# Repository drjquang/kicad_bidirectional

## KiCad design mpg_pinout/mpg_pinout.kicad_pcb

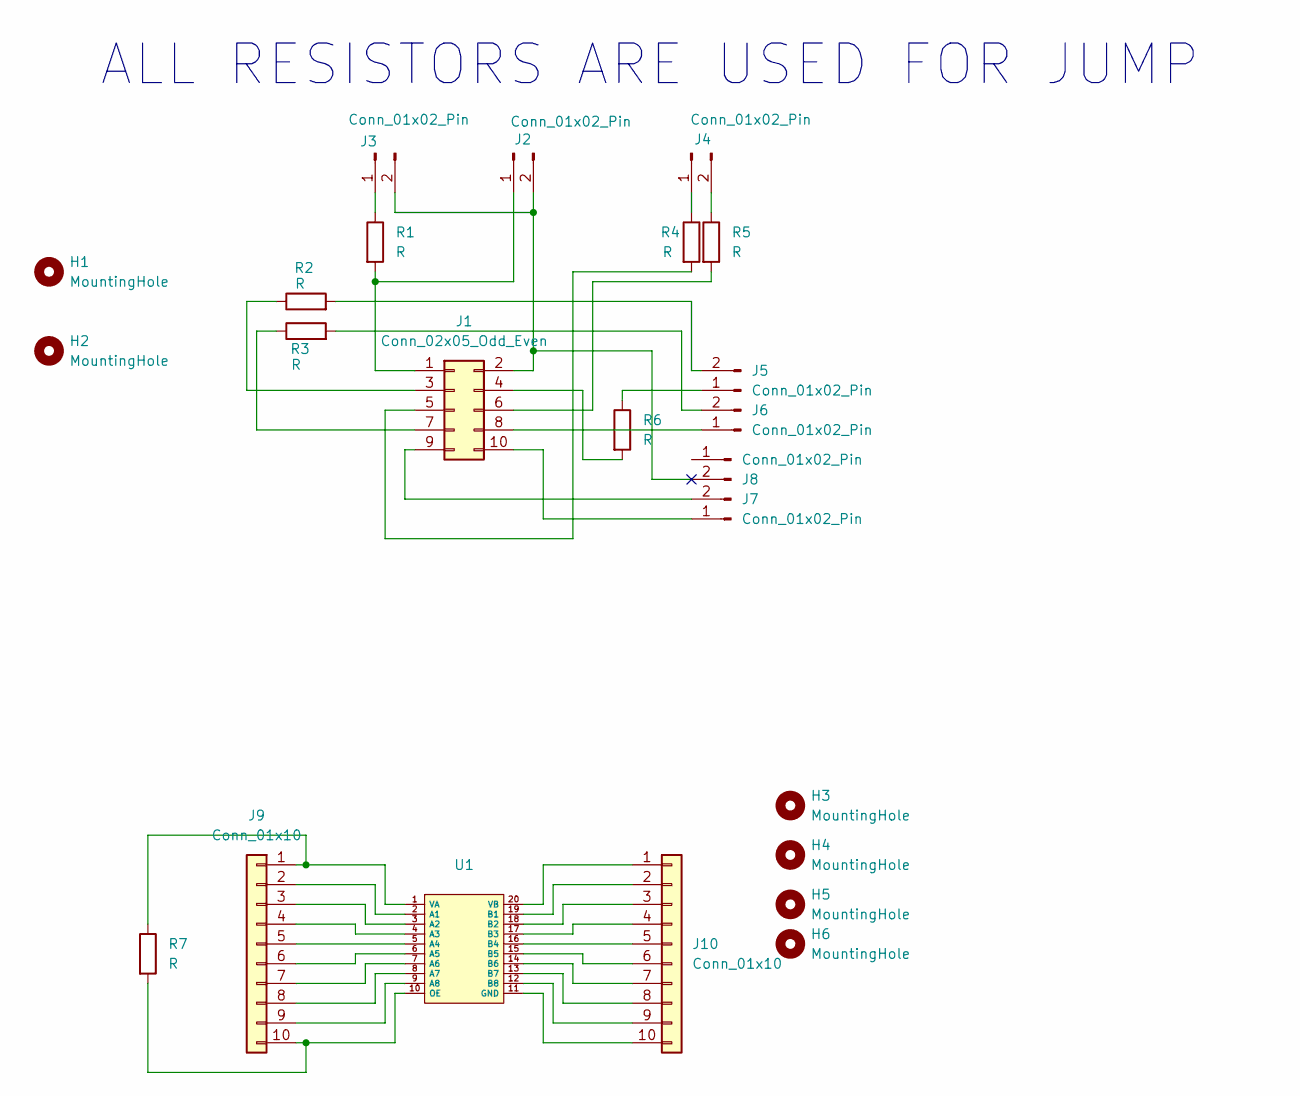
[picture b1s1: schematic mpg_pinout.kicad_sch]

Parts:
H1, H2, H3, H4, H5, H6: MountingHole; hole_3mm
J1: Conn_02x05_Odd_Even; IDC-Header_2x05_P2.54mm_Latch_Vertical
J2, J3, J4, J5, J6, J7, J8: Conn_01x02_Pin; connector_02_508
J9, J10: Conn_01x10; connector_01x10_508
R1: R; R_Axial_DIN0207_L6.3mm_D2.5mm_P10.16mm_Horizontal
R2, R3, R5, R6: R; R_Axial_DIN0414_L11.9mm_D4.5mm_P15.24mm_Horizontal
R4: R; R_Axial_DIN0414_L11.9mm_D4.5mm_P25.40mm_Horizontal
R7: R; R_Axial_DIN0411_L9.9mm_D3.6mm_P25.40mm_Horizontal
U1: TXS0108

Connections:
unnamed: J1.1, J2.1, R1.2
unnamed: J1.3, R2.1
unnamed: J1.4, R6.2
unnamed: J1.5, R4.2
unnamed: J1.6, R5.2
unnamed: J1.7, R3.1
unnamed: J1.8, J6.1
unnamed: J1.9, J7.2
unnamed: J1.10, J7.1
unnamed: J3.1, R1.1
unnamed: J4.1, R4.1
unnamed: J4.2, R5.1
unnamed: J5.1, R6.1
unnamed: J5.2, R2.2
unnamed: J6.2, R3.2
unnamed: J9.1, R7.1, U1.1 (VA)
unnamed: J9.2, U1.2 (A1)
unnamed: J9.3, U1.3 (A2)
unnamed: J9.4, U1.4 (A3)
unnamed: J9.5, U1.5 (A4)
unnamed: J9.6, U1.6 (A5)
unnamed: J9.7, U1.7 (A6)
unnamed: J9.8, U1.8 (A7)
unnamed: J9.9, U1.9 (A8)
unnamed: J9.10, R7.2, U1.10 (OE)
unnamed: J10.1, U1.20 (VB)
unnamed: J10.2, U1.19 (B1)
unnamed: J10.3, U1.18 (B2)
unnamed: J10.4, U1.17 (B3)
unnamed: J10.5, U1.16 (B4)
unnamed: J10.6, U1.15 (B5)
unnamed: J10.7, U1.14 (B6)
unnamed: J10.8, U1.13 (B7)
unnamed: J10.9, U1.12 (B8)
unnamed: J10.10, U1.11 (GND)

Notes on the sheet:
ALL RESISTORS ARE USED FOR JUMP

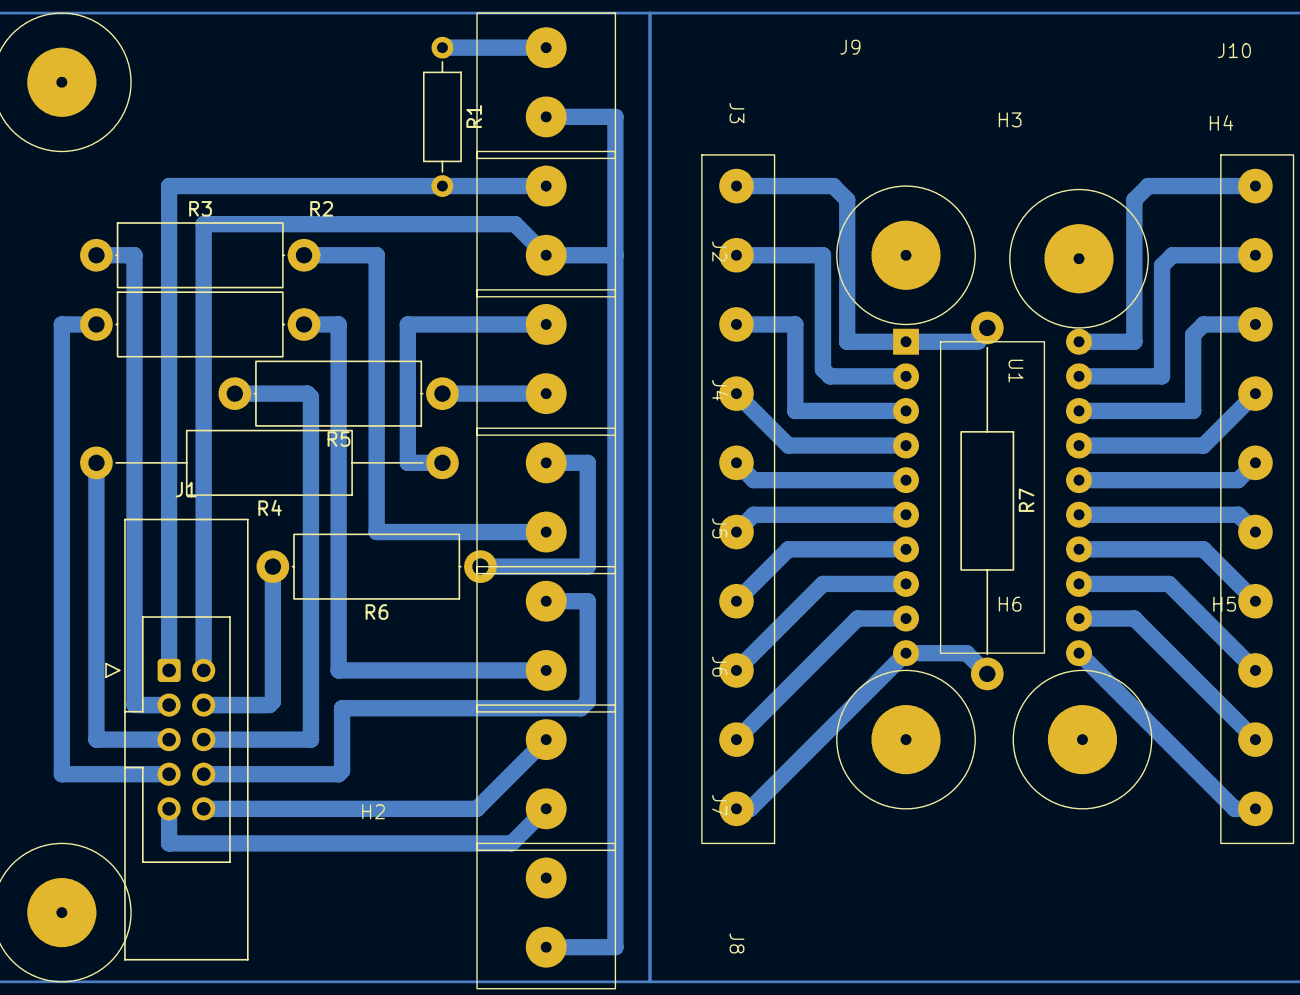
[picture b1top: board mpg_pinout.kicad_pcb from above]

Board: 2 copper layers, 24 parts (0 on the bottom side), 35 nets.

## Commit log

2025-05-21 third commit
2025-05-21 Made pdf file for mpg and bidirectional, 7x10cm
